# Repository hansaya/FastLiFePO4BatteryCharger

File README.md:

Fast battery charger designed to work with LifePo4 batteries using bq24630.

Features
* Selectable battery configuration. Up to 7S.
* Charge management based on temperature. Covers cold and warm conditions.
* Automatic system output selection based on power input conditions.
* No back feeding the input.
* High charging current up to 10A.
* Adjustable max input current limit.
* Adjustable max output current.
* Adjustable charge termination current.
* External enable pin can be used to turn on the charger. This is useful when you want to use the car ignition switch to trigger the charging.

More info at https://www.ti.com/lit/ds/symlink/bq24630.pdf?ts=1594663051247&ref_url=https%253A%252F%252Fwww.ti.com%252Fproduct%252FBQ24630

# Disclaimer

**I’m not responsible for any life or property damage. Do your own research and use my design at your own risk. Lithium batteries can be dangerous.**

# My use case

I currently own an dash cam that can record time lapses while car is parked. This is a great feature and find it to be useful. However this requires the camera to be connected to constant power source. Plugging a camera into car battery permanently will get you a empty battery eventually. Specially if you don’t start the car every day. My solution to this problem is to have an secondary battery pack that powers the camera. 

My requirements:
1) Fast charge the battery within 20min or so. ie within in my daily commute.
2) Battery pack needs to handle the high heat and subzero conditions safely.
3) Runs system like a UPS. No interruptions to the output.
4) High charge cycles so that system would last for a long time.

# Design consideration.
1)	Picked bq24630 ic by TI as the solution to this problem. Which covers all my asks.
2)	Picked LifePo4 battery pack for temperature and charge cycle resiliency. Plus less like to detonate inside the car.
3)	2-layes 1oz board to make PCB house manufacturing cost down.
4)	Went with 3S configuration to keep the battery voltage bellow the input voltage. Bq24630 only a buck converter so it needs some head room.
5)	Keep the battery management work out of this design for simplicity.

# Board files

You can use the zip file within cam/ folder to get the board made by a PCB house. Board can be made with 2-layer and 1oz copper. If you have the money for higher copper thickness go for it but not required. 

## Assembling the board

* Do SMT soldering for all parts except for connectors and the fuse holders. 
* Trim pots are not required but recommended if you want to tweak the current settings. If you do select the trim ports, **DO NOT INSTALL R4, R5, R16, R17, R18 and R19.** R4 and R5 is used to set the charging current, R17 and R17 for termination current and finally R18 and R19 is for adapter current limit. Default values set on schematic designed for 4A adapter current limit, 3A charging current limit and 0.3A termination current.
* NTC thermistor required to let the charger operate at full current. 1.9v at the NTC positive legs could trigger into normal operation mode for testing.
* Add solder to no mask section to increase the current capabilities. This is how I got away with 1oz copper.
* R13 and R14 can be used to set the output voltage. Use 1.8(1+R13/R14) to set the voltage. My schematic sets this at 10.8V (LifePo4 3S).
* C11 can be used to set the safety timer. Checkout the datasheet for more information.
* P-CH mosfets I picked are only designed for 20v so do not exceed 20v input voltage.
* LED outputs are not required but handy to have.
* EN solder jumper can be used to permanently turn on the input.
* TB1 cab be used to reroute the charge enable pin to the external connector. Use a sharp knife to cut the trace between default charge enable tab.
* Q7 is optional if the charger needs to be enabled by default. Use a jumper to bridge the mosfet pads.

# Other considerations

* Install an external battery protection system between the battery and the charger. 
* Even though charger can do 10A, inductor seems to get bit toasty at that level of current. I find 6A to be a happy medium.

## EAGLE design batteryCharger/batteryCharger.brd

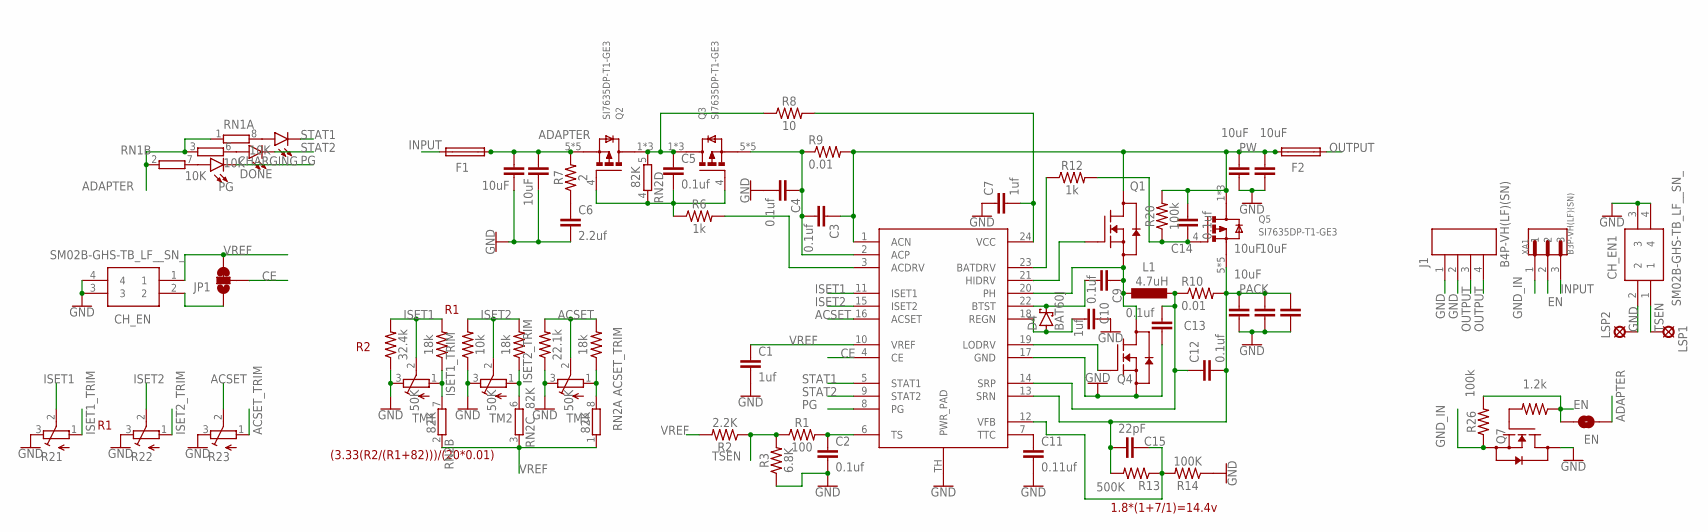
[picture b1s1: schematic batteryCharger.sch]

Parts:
C1, C7, C10: 1uf; C0603
C2, C3, C4, C5, C9, C12, C13, C14: 0.1uf; C0603
C6: 2.2uf; C0603
C11: 0.11uf; C0603
C15: 22pF; C0603
C16, C17, C18, C19, C20, C21, C22: 10uF; C1206
CHARGING: LED1206; LED-1206
CH_EN, CH_EN1: SM02B-GHS-TB_LF__SN_; SM02BGHSTBLFSN
D4: BAT60J; SOD323_ST
DONE: LED1206; LED-1206
EN: JUMPER-SMT_2_NO_SILK; SMT-JUMPER_2_NO_SILK
F1, F2: SMD-MICRO-FUSE-BLOCK; OMNIBLOK
J1: B4P-VH(LF)(SN); JST_B4P-VH(LF)(SN)
JP1: JUMPER-SMT_3_1-NC_TRACE_NO-SILK; SMT-JUMPER_3_1-NC_TRACE_NO-SILK
L1: 4.7uH; CEP125
LSP1, LSP2: LSP10
PG: LED1206; LED-1206
Q1, Q4, Q7: SIR414DP-T1-GE3; TRANS_SQJ461EP-T1-GE3
Q2, Q3, Q5: SI7635DP-T1-GE3; TRANS_SI7635DP-T1-GE3
R1: 100; 0603
R2: 2.2K; 0603
R3: 6.8K; 0603
R4: 32.4k; 0603
R5, R17, R19: 18k; 0603
R6, R12: 1k; 0603
R7: 2; 0603
R8: 10; 0603
R9, R10: 0.01; R1206
R13: 500K; 0603
R14: 100K; 0603
R16: 10k; 0603
R18: 22.1k; 0603
R20, R26: 100k; 0603
R21, R22, R23: TRIM_EU-3223W; 3223W
R25: 1.2k; 0603
RN1: 10K; 0603-ARC
RN2: 82K; CAY16
TM1, TM2, TM3: 50K; TC33X
U$1: BQ24630VQFN24; HVQFN24
XA1: B3P-VH(LF)(SN); JST_B3P-VH(LF)(SN)

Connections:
ACSET: R18.2, R19.2, R23.2 (S), TM3.2 (S), U$1.16 (ACSET)
ACSET_TRIM: R19.1, R23.1 (A), RN2.8 (2), TM3.1 (A)
ADAPTER: C21.1, C22.1, EN.1, F1.P$1 (1), Q2.5 (D), Q2.6 (D), Q2.7 (D), Q2.8 (D), Q2.9 (D), R7.2, RN1.1, RN1.2 (1), RN1.3 (1)
CE: JP1.2, U$1.4 (CE)
EN: EN.2, R25.1, R26.2, XA1.2
GND: C1.2, C2.2, C4.2, C6.2, C7.1, C10.2, C11.2, C13.1, C16.2, C17.2, C18.2, C19.2, C20.2, C21.2, C22.2, CH_EN.3, CH_EN.4, CH_EN1.2, CH_EN1.3, CH_EN1.4, J1.1, J1.2, LSP2.MP, Q4.1 (S), Q4.2 (S), Q4.3 (S), Q7.5 (D), Q7.6 (D), Q7.7 (D), Q7.8 (D), Q7.9 (D), R3.1, R4.1, R14.1, R16.1, R18.1, R21.3 (E), R22.3 (E), R23.3 (E), TM1.3 (E), TM2.3 (E), TM3.3 (E), U$1.17 (GND), U$1.TH (PWR_PAD)
GND_IN: Q7.1 (S), Q7.2 (S), Q7.3 (S), R26.1, XA1.1
INPUT: F1.P$2 (2), XA1.3
ISET1: R4.2, R5.2, R21.2 (S), TM1.2 (S), U$1.11 (ISET1)
ISET1_TRIM: R5.1, R21.1 (A), RN2.7 (2), TM1.1 (A)
ISET2: R16.2, R17.2, R22.2 (S), TM2.2 (S), U$1.15 (ISET2)
ISET2_TRIM: R17.1, R22.1 (A), RN2.6 (2), TM2.1 (A)
unnamed: C2.1, R1.2, U$1.6 (TS)
unnamed: CHARGING.A, RN1.8 (2)
unnamed: CH_EN.2, JP1.1
unnamed: Q7.4 (G), R25.2
unnamed: DONE.A, RN1.6 (2)
unnamed: PG.A, RN1.7 (2)
unnamed: C9.2, D4.C, U$1.22 (BTST)
unnamed: C5.1, Q2.1 (S), Q2.2 (S), Q2.3 (S), Q3.1 (S), Q3.2 (S), Q3.3 (S), R8.1, RN2.5 (2)
unnamed: R6.2, U$1.3 (ACDRV)
unnamed: C3.2, C4.1, Q3.5 (D), Q3.6 (D), Q3.7 (D), Q3.8 (D), Q3.9 (D), R9.1, U$1.2 (ACP)
unnamed: C15.1, R13.1, R14.2, U$1.12 (VFB)
unnamed: C7.2, R8.2, U$1.24 (VCC)
unnamed: Q1.4 (G), U$1.21 (HIDRV)
unnamed: C6.1, R7.1
unnamed: C12.1, C13.2, L1.2, R10.1, U$1.14 (SRP)
unnamed: C10.1, D4.A, U$1.18 (REGN)
unnamed: Q4.4 (G), U$1.19 (LODRV)
unnamed: C9.1, L1.1, Q1.1 (S), Q1.2 (S), Q1.3 (S), Q4.5 (D), Q4.6 (D), Q4.7 (D), Q4.8 (D), Q4.9 (D), U$1.20 (PH)
unnamed: C11.1, U$1.7 (TTC)
unnamed: C14.1, Q5.4 (G), R12.2, R20.1
unnamed: C5.2, Q2.4 (G), Q3.4 (G), R6.1, RN2.4 (1)
unnamed: R12.1, U$1.23 (BATDRV)
OUTPUT: F2.P$1 (1), J1.3, J1.4
PACK: C12.2, C15.2, C16.1, C17.1, C18.1, Q5.5 (D), Q5.6 (D), Q5.7 (D), Q5.8 (D), Q5.9 (D), R10.2, R13.2, U$1.13 (SRN)
PG: PG.C, U$1.8 (PG)
PW: C3.1, C14.2, C19.1, C20.1, F2.P$2 (2), Q1.5 (D), Q1.6 (D), Q1.7 (D), Q1.8 (D), Q1.9 (D), Q5.1 (S), Q5.2 (S), Q5.3 (S), R9.2, R20.2, U$1.1 (ACN)
STAT1: CHARGING.C, U$1.5 (STAT1)
STAT2: DONE.C, U$1.9 (STAT2)
TSEN: CH_EN1.1, LSP1.MP, R1.1, R2.1, R3.2
VREF: C1.1, CH_EN.1, JP1.3, R2.2, RN2.1, RN2.2 (1), RN2.3 (1), U$1.10 (VREF)

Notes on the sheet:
1.8*(1+7/1)=14.4v
(3.33(R2/(R1+82)))/(20*0.01)

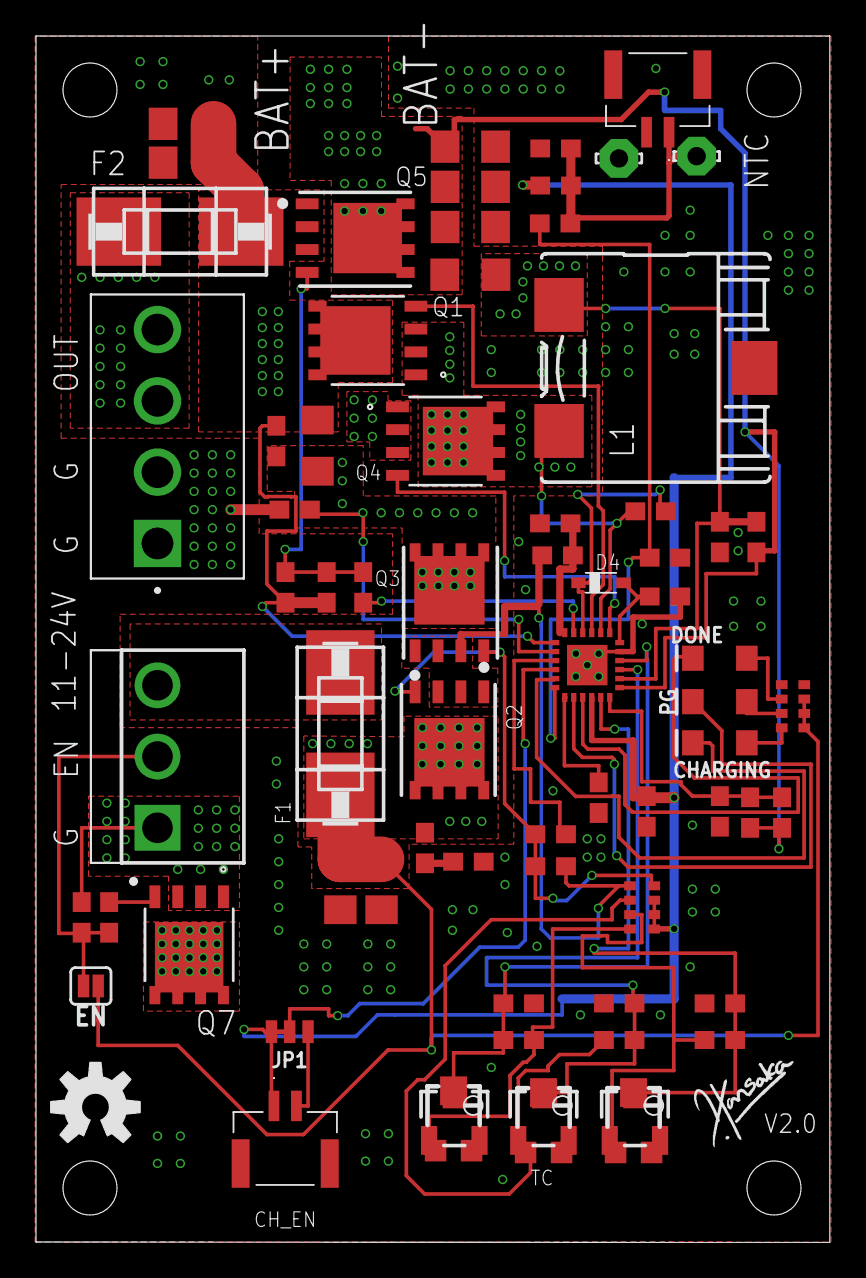
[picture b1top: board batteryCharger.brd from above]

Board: 2 copper layers, 44.1 x 67.0 mm, 73 parts (0 on the bottom side), 42 nets.

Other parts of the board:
U$2: SIGNATURE
U$3: OSHW-LOGO-M

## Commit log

2020-07-01 final board file
2020-07-11 v2 with bug fixses
2020-07-13 Bug fixses
2020-07-13 Add eagle libs for charger and connectors
2020-07-13 Create LICENSE
2020-07-20 Change the enable pin design
2020-07-20 Clean up
2020-07-20 doc mistakes
2020-08-06 final v2

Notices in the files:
parts and their libraries:
SparkFun-LED: Licensing: Creative Commons ShareAlike 4.0 International - https://creativecommons.org/licenses/by-sa/4.0
